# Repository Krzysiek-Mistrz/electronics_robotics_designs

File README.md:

# My Electronics Repository

Welcome to my electronics repository! This is the place where I store all my ppcbs, models and code for some of my projects1.

## Overview

This repository serves as a central hub for all the mechanical side of my robotic and automatic projects. It includes pcbs, models, and codes. Here, you will find a diverse collection of my works.

## Contents

The repository is organized by ECAD programs in which I have designed my PCBS and project type. In these folders you will find each project associated with this program. There's also models folder in which I have prepared all my models for my projects in CAD programs like SOLIDWORKS or INVENTOR.

- **Altium**
  - PCBs
- **Kicad**
  - PCBs
- **Models**
  - CAD models of robots
- **Codes**
  - Code for my projects

## Getting Started

To get started with any of the projects, follow these steps:

1. **Clone the repository**:
    ```bash
    git clone https://github.com/Krzysiek-Mistrz/<name_of_repo>.git
    ```

2. **Navigate to the project directory**:
    ```bash
    cd your-repo-name/project-directory
    ```

3. **Follow the specific project instructions**:
    Each project may have its own README file with detailed instructions on how to set up and run the code.

## Contributing

This repo is only showcase of my work, You don't have to contribute to it. If you have any suggestions on what should I improve please contact me via github :)

## Contact

If you have any questions or suggestions, feel free to reach out to me:
- GitHub: [Krzysiek-Mistrz](https://github.com/Krzysiek-Mistrz)

Thank you for visiting my repository! I hope you find the code here useful and informative.

## License

This repository is licensed under the GNU GPL V3. See the LICENSE file for more details.  

GNU GPL V3 @ Krzychu 2025

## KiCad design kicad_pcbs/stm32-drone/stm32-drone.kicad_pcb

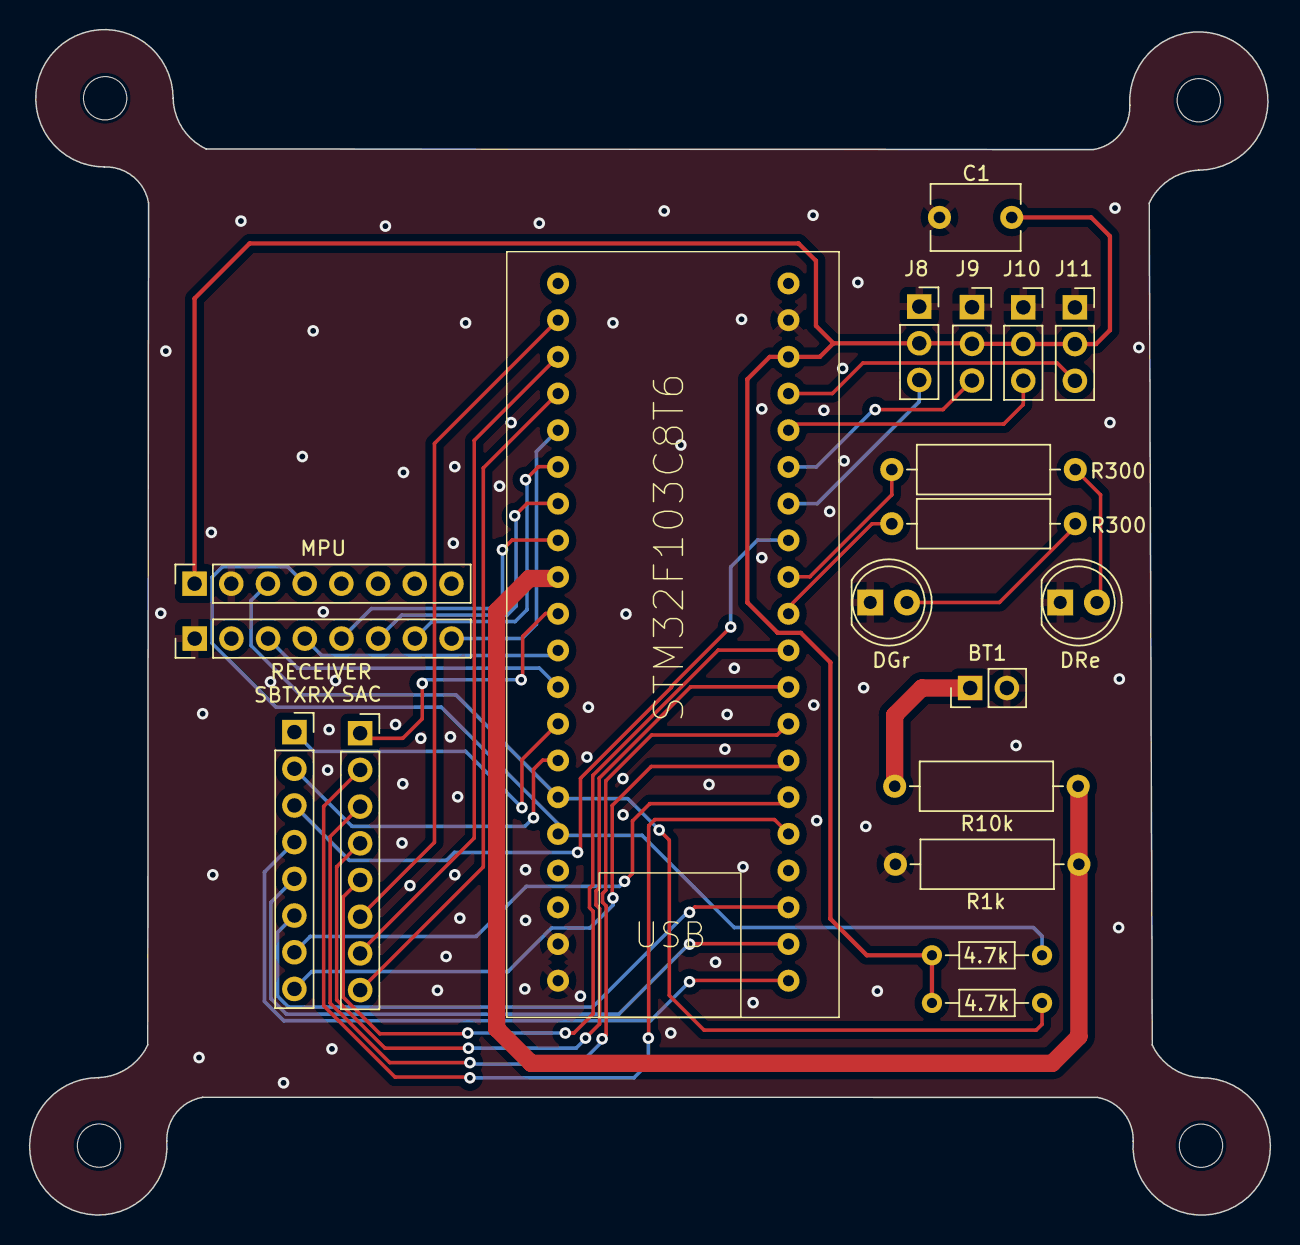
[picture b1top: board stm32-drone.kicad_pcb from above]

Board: 2 copper layers, 85.9 x 82.1 mm, 19 parts (0 on the bottom side), 36 nets.

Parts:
4.7k, 4.7k#2: 4.7k; R_Axial_DIN0204_L3.6mm_D1.6mm_P7.62mm_Horizontal
BT1: Battery; PinHeader_1x02_P2.54mm_Vertical
C1: C; C_Disc_D6.0mm_W4.4mm_P5.00mm
DGr: LED; LED_D5.0mm
DRe: LED; LED_D5.0mm
J6: RECEIVER; PinHeader_1x08_P2.54mm_Vertical
J8: ESC1 VGS; PinSocket_1x03_P2.54mm_Vertical
J9: ESC2 VGS; PinSocket_1x03_P2.54mm_Vertical
J10: ESC3 VGS; PinSocket_1x03_P2.54mm_Vertical
J11: ESC4 VGS; PinSocket_1x03_P2.54mm_Vertical
MPU: mpu6050 socket pins; PinSocket_1x08_P2.54mm_Vertical
R1k, R10k, R300, R300#2: R; R_Axial_DIN0309_L9.0mm_D3.2mm_P12.70mm_Horizontal
SAC: connector socket 1; PinSocket_1x08_P2.54mm_Vertical
SBTXRX: connector socket 2; PinSocket_1x08_P2.54mm_Vertical
U1: STM32F103C8Tx; stm32f103

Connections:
+5V: 4.7k.1, 4.7k#2.1, C1.1, J8.2, J9.2, J10.2, J11.2, MPU.1, U1.24 (VDD)
/BATT_ANALOG: R1k.2, R10k.1, U1.14 (PA4)
/C13: SAC.6, U1.2 (PC13)
/C14: SAC.7, U1.3 (PC14)
/C15: SAC.8, U1.4 (PC15)
/CH1: J6.8, U1.10 (PA0)
/CH2: J6.7, U1.11 (PA1)
/CH3: J6.6, U1.12 (PA2)
/CH4: J6.5, U1.13 (PA3)
/CH5: J6.4, U1.16 (PA6)
/CH6: J6.3, U1.17 (PA7)
/ESC1: J8.3, U1.42 (PB6)
/ESC2: J9.3, U1.43 (PB7)
/ESC3: J10.3, U1.45 (PB8)
/ESC4: J11.3, U1.46 (PB9)
/PA5: SAC.1, U1.15 (PA5)
/PA8: SAC.2, U1.29 (PA8)
/PA11: SAC.3, U1.32 (PA11)
/PA12: SAC.4, U1.33 (PA12)
/PA15: SAC.5, U1.38 (PA15)
/PB0: SBTXRX.1, U1.18 (PB0)
/PB1: SBTXRX.2, U1.19 (PB1)
/PB3: R300.1, U1.39 (PB3)
/PB4: R300#2.1, U1.40 (PB4)
/PB5: SBTXRX.3, U1.41 (PB5)
/PB12: SBTXRX.4, U1.25 (PB12)
/PB13: SBTXRX.5, U1.26 (PB13)
/PB14: SBTXRX.6, U1.27 (PB14)
/RX: SBTXRX.7, U1.30 (PA9)
/SCL: 4.7k.2, MPU.3, U1.21 (PB10)
/SDA: 4.7k#2.2, MPU.4, U1.22 (PB11)
/TX: SBTXRX.8, U1.31 (PA10)
GND: BT1.2 (-), C1.2, DGr.1 (K), DRe.1 (K), J6.1, J8.1, J9.1, J10.1, J11.1, MPU.2, R1k.1, U1.23 (VSS)
unnamed: DGr.2 (A), R300.2
unnamed: DRe.2 (A), R300#2.2
VCC: BT1.1 (+), R10k.2

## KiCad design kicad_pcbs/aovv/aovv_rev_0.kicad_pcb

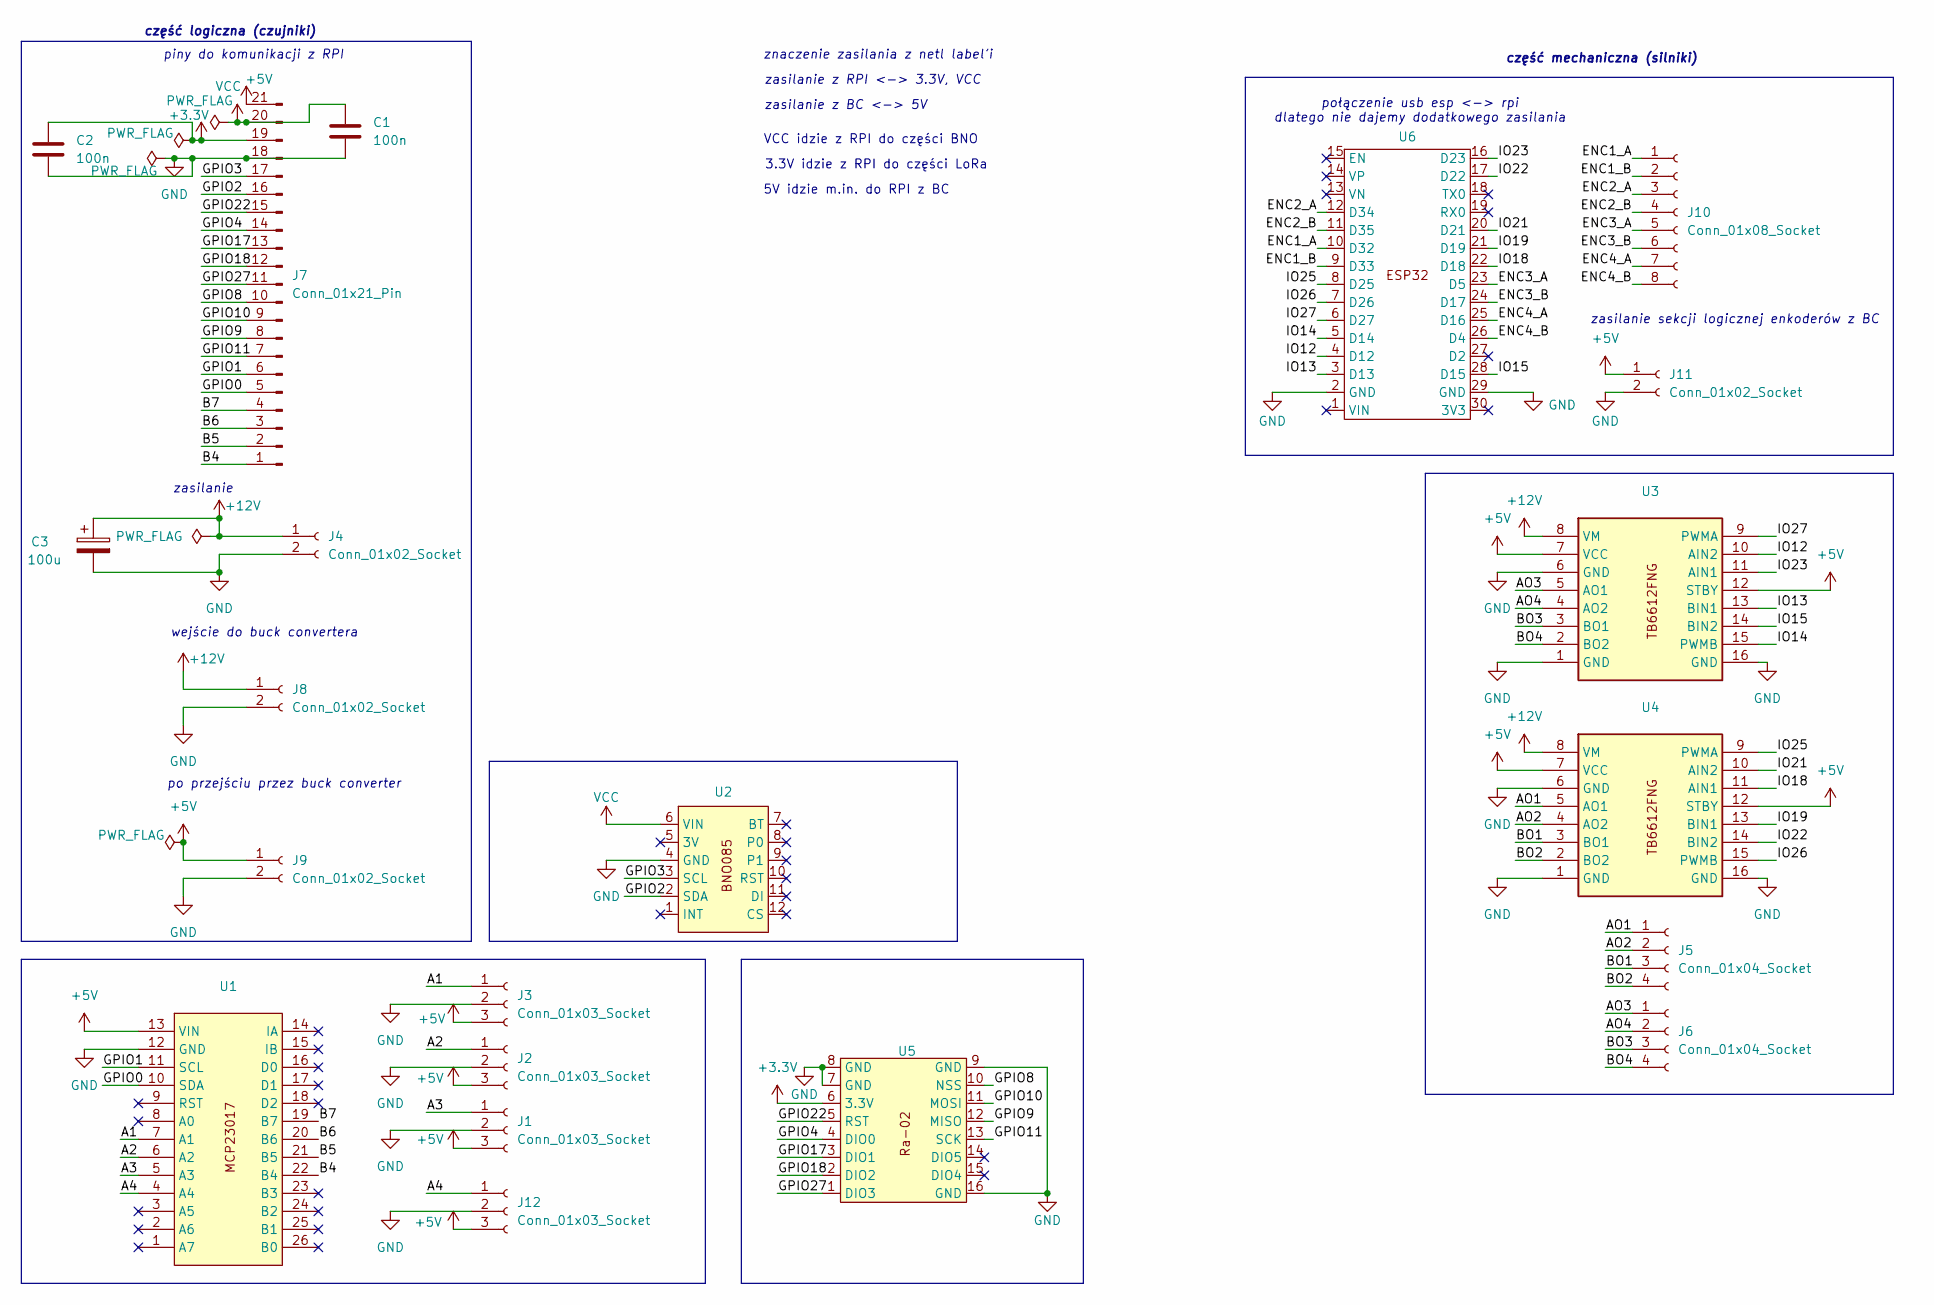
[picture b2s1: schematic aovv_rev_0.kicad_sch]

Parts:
C1, C2: 100n; C_Disc_D11.0mm_W5.0mm_P5.00mm
C3: 100u; CP_Radial_D8.0mm_P2.50mm
J1, J2, J3, J12: Conn_01x03_Socket; PinSocket_1x03_P2.54mm_Vertical
J4, J8, J9, J11: Conn_01x02_Socket; PinSocket_1x02_P2.54mm_Vertical
J5, J6: Conn_01x04_Socket; PinSocket_1x04_P2.54mm_Vertical
J7: Conn_01x21_Pin; PinHeader_1x21_P2.54mm_Vertical
J10: Conn_01x08_Socket; PinSocket_1x08_P2.54mm_Vertical
U1: MCP23017_THT
U2: BNO085_THT
U3, U4: TB6612FNG_THT
U5: Ra-02_THT
U6: ESP32_THT

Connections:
+3.3V: C2.2, J7.19, U5.6 (3.3V)
+5V: J1.3, J2.3, J3.3, J7.21, J9.1, J11.1, J12.3, U1.13 (VIN), U3.7 (VCC), U3.12 (STBY), U4.7 (VCC), U4.12 (STBY)
+12V: C3.1, J4.1, J8.1, U3.8 (VM), U4.8 (VM)
/A1: J3.1, U1.7 (A1)
/A2: J2.1, U1.6 (A2)
/A3: J1.1, U1.5 (A3)
/A4: J12.1, U1.4 (A4)
/AO1: J5.1, U4.5 (AO1)
/AO2: J5.2, U4.4 (AO2)
/AO3: J6.1, U3.5 (AO1)
/AO4: J6.2, U3.4 (AO2)
/B4: J7.1, U1.22 (B4)
/B5: J7.2, U1.21 (B5)
/B6: J7.3, U1.20 (B6)
/B7: J7.4, U1.19 (B7)
/BO1: J5.3, U4.3 (BO1)
/BO2: J5.4, U4.2 (BO2)
/BO3: J6.3, U3.3 (BO1)
/BO4: J6.4, U3.2 (BO2)
/ENC1_A: J10.1, U6.10 (D32)
/ENC1_B: J10.2, U6.9 (D33)
/ENC2_A: J10.3, U6.12 (D34)
/ENC2_B: J10.4, U6.11 (D35)
/ENC3_A: J10.5, U6.23 (D5)
/ENC3_B: J10.6, U6.24 (D17)
/ENC4_A: J10.7, U6.25 (D16)
/ENC4_B: J10.8, U6.26 (D4)
/GPIO0: J7.5, U1.10 (SDA)
/GPIO1: J7.6, U1.11 (SCL)
/GPIO2: J7.16, U2.2 (SDA)
/GPIO3: J7.17, U2.3 (SCL)
/GPIO4: J7.14, U5.4 (DIO0)
/GPIO8: J7.10, U5.10 (NSS)
/GPIO9: J7.8, U5.12 (MISO)
/GPIO10: J7.9, U5.11 (MOSI)
/GPIO11: J7.7, U5.13 (SCK)
/GPIO17: J7.13, U5.3 (DIO1)
/GPIO18: J7.12, U5.2 (DIO2)
/GPIO22: J7.15, U5.5 (RST)
/GPIO27: J7.11, U5.1 (DIO3)
/IO12: U3.10 (AIN2), U6.4 (D12)
/IO13: U3.13 (BIN1), U6.3 (D13)
/IO14: U3.15 (PWMB), U6.5 (D14)
/IO15: U3.14 (BIN2), U6.28 (D15)
/IO18: U4.11 (AIN1), U6.22 (D18)
/IO19: U4.13 (BIN1), U6.21 (D19)
/IO21: U4.10 (AIN2), U6.20 (D21)
/IO22: U4.14 (BIN2), U6.17 (D22)
/IO23: U3.11 (AIN1), U6.16 (D23)
/IO25: U4.9 (PWMA), U6.8 (D25)
/IO26: U4.15 (PWMB), U6.7 (D26)
/IO27: U3.9 (PWMA), U6.6 (D27)
GND: C1.2, C2.1, C3.2, J1.2, J2.2, J3.2, J4.2, J7.18, J8.2, J9.2, J11.2, J12.2, U1.12 (GND), U2.4 (GND), U3.1 (GND), U3.6 (GND), U3.16 (GND), U4.1 (GND), U4.6 (GND), U4.16 (GND), U5.7 (GND), U5.8 (GND), U5.9 (GND), U5.16 (GND), U6.2 (GND), U6.29 (GND)
VCC: C1.1, J7.20, U2.6 (VIN)

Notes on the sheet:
zasilanie z RPI <-> 3.3V, VCC
3.3V idzie z RPI do części LoRa
połączenie usb esp <-> rpi dlatego nie dajemy dodatkowego zasilania
zasilanie z BC <-> 5V
część logiczna (czujniki)
wejście do buck convertera
piny do komunikacji z RPI
VCC idzie z RPI do części BNO
zasilanie sekcji logicznej enkoderów z BC
znaczenie zasilania z netl label'i
część mechaniczna (silniki)
zasilanie
5V idzie m.in. do RPI z BC
po przejściu przez buck converter

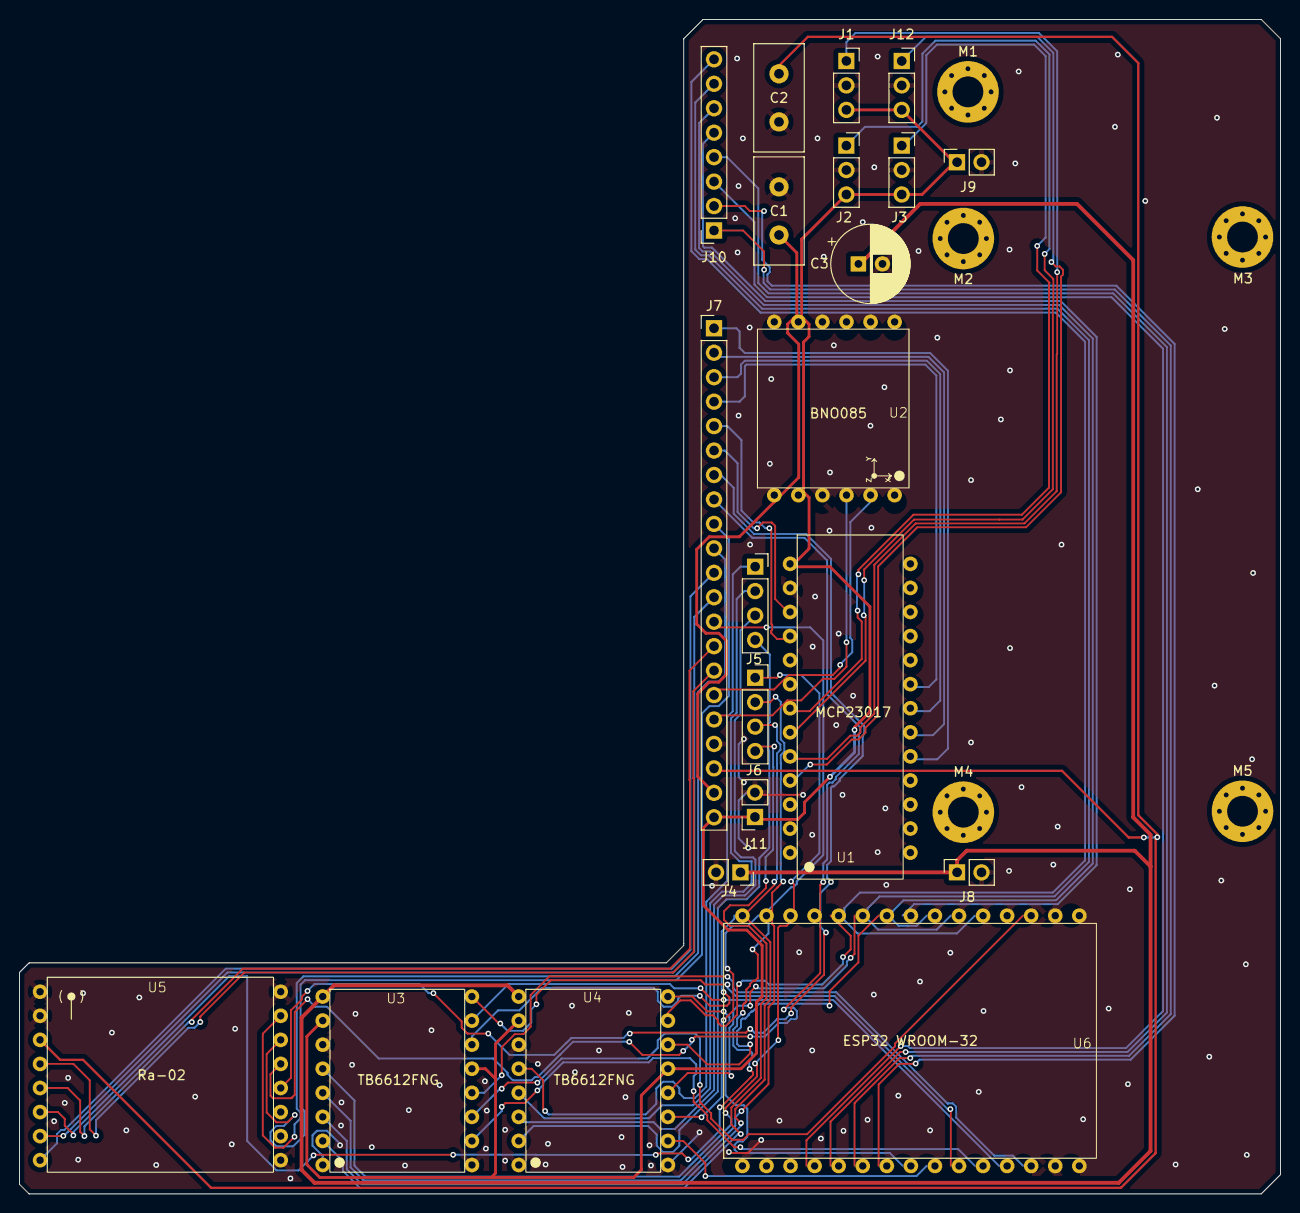
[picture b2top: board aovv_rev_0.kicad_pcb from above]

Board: 2 copper layers, 131.0 x 122.0 mm, 26 parts (0 on the bottom side), 54 nets.

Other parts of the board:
M1, M2, M3, M4, M5: MountingHole_3.2mm_M3_Pad_Via

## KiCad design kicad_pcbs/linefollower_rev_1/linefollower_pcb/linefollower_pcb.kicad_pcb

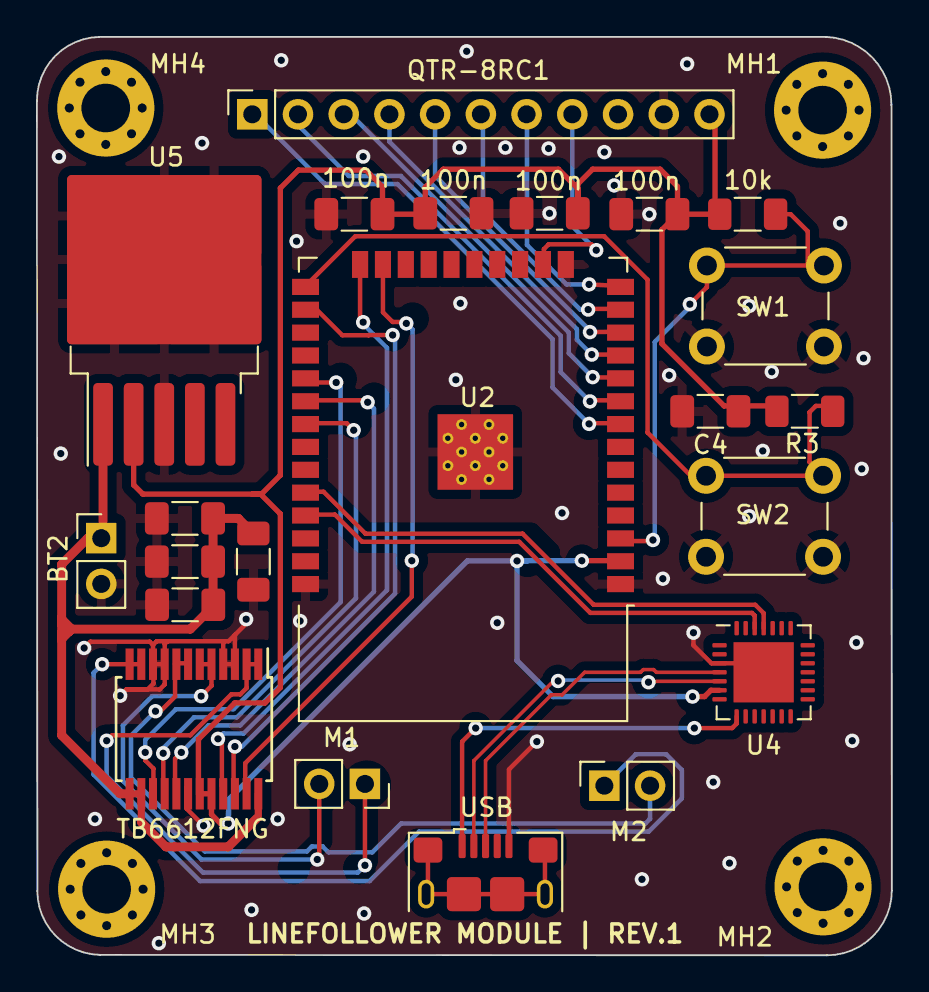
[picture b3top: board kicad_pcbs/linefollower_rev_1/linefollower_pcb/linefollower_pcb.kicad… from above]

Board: 2 copper layers, 47.5 x 51.0 mm, 26 parts (0 on the bottom side), 28 nets.

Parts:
10k: 10k; R_1206_3216Metric_Pad1.30x1.75mm_HandSolder
100n: C_Unpolarized; C_1206_3216Metric_Pad1.33x1.80mm_HandSolder
100n#2, 100n#3: C; C_1206_3216Metric_Pad1.33x1.80mm_HandSolder
100u1, 200u1: C_Polarized; C_1206_3216Metric_Pad1.33x1.80mm_HandSolder
BT2: Battery; PinHeader_1x02_P2.54mm_Vertical
C1, C5: 100n; C_1206_3216Metric_Pad1.33x1.80mm_HandSolder
C2, C4: 10u; C_1206_3216Metric_Pad1.33x1.80mm_HandSolder
M1, M2: Conn_01x02_Socket; PinSocket_1x02_P2.54mm_Vertical
MH1, MH2, MH3, MH4: MountingHole_2.7mm_Pad_Via
QTR-8RC1: Conn_01x11_Socket; PinSocket_1x11_P2.54mm_Vertical
R3: 10k; R_1206_3216Metric_Pad1.30x1.75mm_HandSolder
SW1, SW2: SW_Push; SW_PUSH_6mm
U1: TB6612FNG; SSOP-24_5.3x8.2mm_P0.65mm
U2: ESP32-WROOM-32
U4: CP2102N-Axx-xQFN28; QFN-28-1EP_5x5mm_P0.5mm_EP3.35x3.35mm
U5: LM2596S-3.3; TO-263-5_TabPin3
USB: USB_B_Micro; USB_Micro-B_Amphenol_10118193-0001LF_Horizontal

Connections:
/A1: M1.1, U1.1 (AO1), U1.2 (AO1)
/A2: M1.2, U1.5 (AO2), U1.6 (AO2)
/B1: M2.1, U1.11 (BO1), U1.12 (BO1)
/B2: M2.2, U1.7 (BO2), U1.8 (BO2)
/BOOT: R3.1, SW2.1, U2.25 (IO0)
/D2: U1.21 (AIN1), U2.24 (IO2)
/D4: U1.22 (AIN2), U2.26 (IO4)
/D5: U1.15 (PWMB), U2.29 (IO5)
/D12: QTR-8RC1.7, U2.14 (IO12)
/D13: QTR-8RC1.8, U2.16 (IO13)
/D14: QTR-8RC1.6, U2.13 (IO14)
/D15: U1.23 (PWMA), U2.23 (IO15)
/D18: U1.17 (BIN1), U2.30 (IO18)
/D19: U1.16 (BIN2), U2.31 (IO19)
/D25: QTR-8RC1.3, U2.10 (IO25)
/D26: QTR-8RC1.4, U2.11 (IO26)
/D27: QTR-8RC1.5, U2.12 (IO27)
/D32: QTR-8RC1.1, U2.8 (IO32)
/D33: QTR-8RC1.2, U2.9 (IO33)
/D+: U4.4 (D+), USB.3 (D+)
/D-: U4.5 (D-), USB.2 (D-)
/EN: 10k.1, SW1.1, U2.3 (EN)
/RX: U2.34 (RXD0/IO3), U4.25 (RXD)
/TX: U2.35 (TXD0/IO1), U4.26 (TXD)
/VBUS: U4.8 (VBUS), USB.1 (VBUS)
GND: 100n.2, 100n#2.2, 100n#3.2, 100u1.2, 200u1.2, BT2.2 (-), C1.2, C2.2, C4.2, C5.1, QTR-8RC1.10, SW1.2, SW2.2, U1.3 (PGND1), U1.4 (PGND1), U1.9 (PGND2), U1.10 (PGND2), U1.18 (GND), U2.1 (GND), U2.15 (GND), U2.38 (GND), U2.39 (GND), U4.3 (GND), U4.29 (GND), U5.3 (GND), USB.5 (GND)
VCC: 10k.2, 100n.1, 100n#2.1, 100n#3.1, C4.1, C5.2, QTR-8RC1.11, R3.2, U1.19 (STBY), U1.20 (VCC), U2.2 (VDD), U4.6 (VDD), U5.2 (OUT)
VDD: 100u1.1, 200u1.1, BT2.1 (+), C1.1, C2.1, U1.13 (VM2), U1.14 (VM3), U1.24 (VM1), U5.1 (VIN)

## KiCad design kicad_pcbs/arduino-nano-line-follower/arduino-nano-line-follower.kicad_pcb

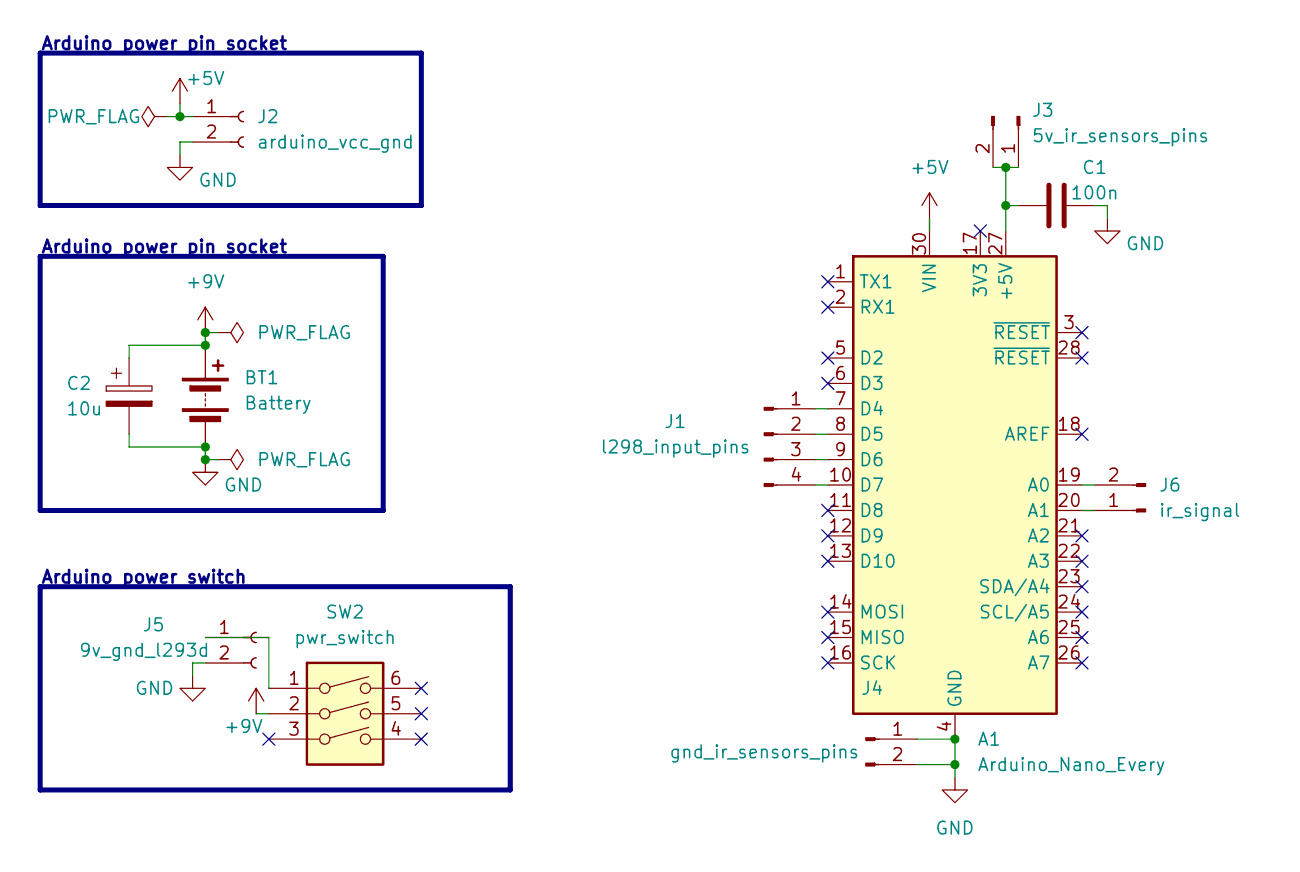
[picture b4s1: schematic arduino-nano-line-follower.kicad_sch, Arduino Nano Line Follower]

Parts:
A1: Arduino_Nano_Every; Arduino_Nano
BT1: Battery; PinSocket_1x02_P2.54mm_Vertical
C1: 100n; C_Disc_D3.0mm_W1.6mm_P2.50mm
C2: 10u; C_Radial_D4.0mm_H5.0mm_P1.50mm
J1: l298_input_pins; PinHeader_1x04_P2.54mm_Vertical
J2: arduino_vcc_gnd; PinSocket_1x02_P2.54mm_Vertical
J3: 5v_ir_sensors_pins; PinHeader_1x02_P2.54mm_Vertical
J4: gnd_ir_sensors_pins; PinHeader_1x02_P2.54mm_Vertical
J5: 9v_gnd_l293d; PinSocket_1x02_P2.54mm_Vertical
J6: ir_signal; PinHeader_1x02_P2.54mm_Vertical
SW2: pwr_switch; SW_NKK_G1xJP

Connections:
+5V: A1.30 (VIN), J2.1
+9V: BT1.1 (+), C2.1, SW2.2
GND: A1.4 (GND), A1.29 (GND), BT1.2 (-), C1.2, C2.2, J2.2, J4.1, J4.2, J5.2; also elsewhere on the board
unnamed: A1.27 (+5V), C1.1, J3.1, J3.2
unnamed: A1.19 (A0), J6.2
unnamed: A1.20 (A1), J6.1
unnamed: A1.7 (D4), J1.1
unnamed: A1.8 (D5), J1.2
unnamed: A1.9 (D6), J1.3
unnamed: A1.10 (D7), J1.4
unnamed 10: J5.1, SW2.1; also elsewhere on the board

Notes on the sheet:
Arduino power pin socket
Arduino power switch

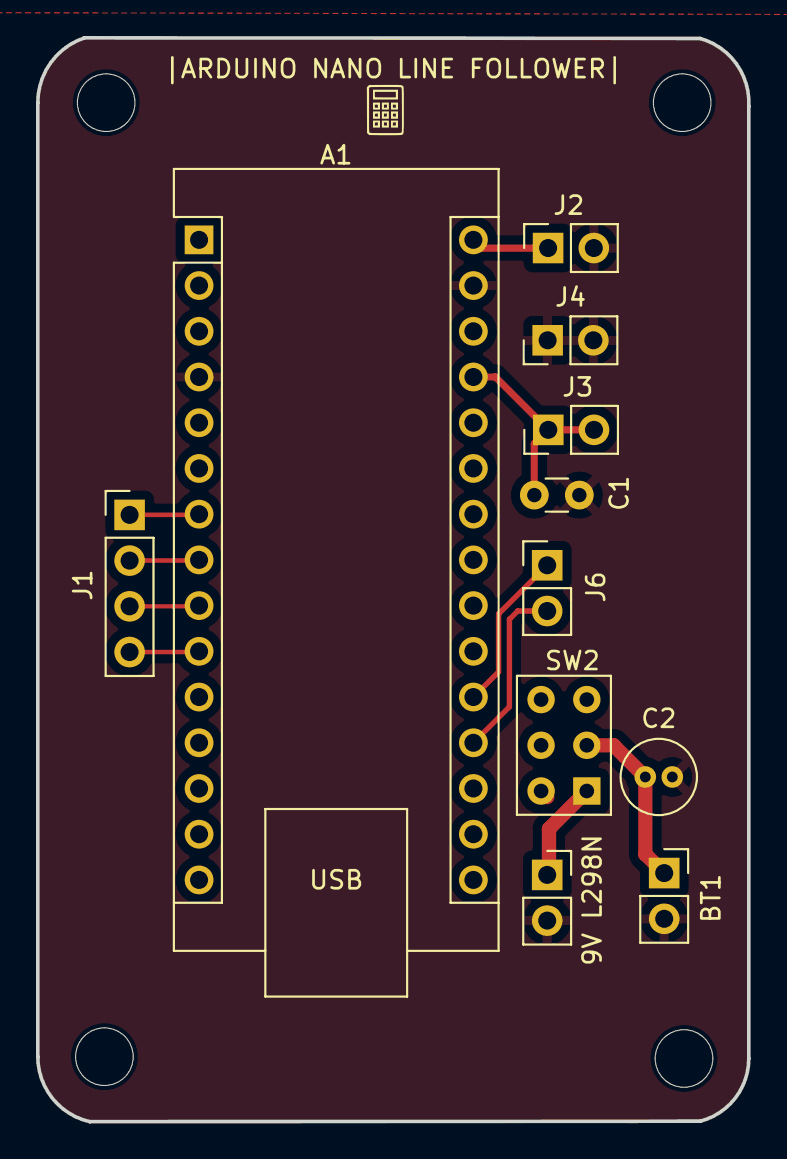
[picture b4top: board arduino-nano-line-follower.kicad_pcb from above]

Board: 2 copper layers, 39.5 x 60.2 mm, 11 parts (0 on the bottom side), 11 nets.

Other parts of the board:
9V L298N: 9v_gnd_l293d; PinSocket_1x02_P2.54mm_Vertical

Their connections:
GND: 9V L298N.2; also elsewhere on the board
unnamed 10: 9V L298N.1; also elsewhere on the board

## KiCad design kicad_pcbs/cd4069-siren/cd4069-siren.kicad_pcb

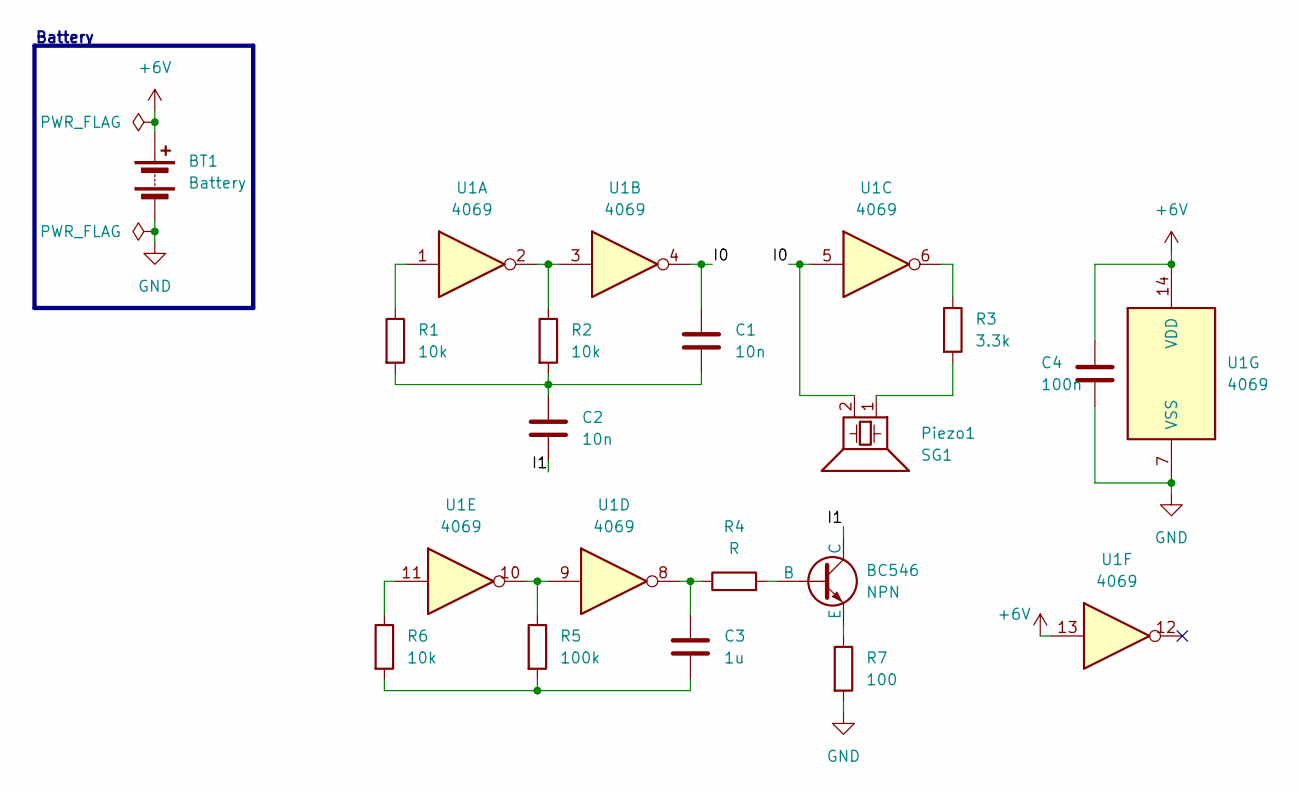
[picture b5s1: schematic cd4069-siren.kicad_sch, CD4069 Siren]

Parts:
BC546: NPN; TO-92
BT1: Battery; PinHeader_1x02_P2.54mm_Vertical
C1, C2: 10n; C_Disc_D3.0mm_W1.6mm_P2.50mm
C3: 1u; C_Disc_D3.0mm_W1.6mm_P2.50mm
C4: 100n; C_Disc_D3.0mm_W1.6mm_P2.50mm
Piezo1: SG1; Buzzer_12x9.5RM7.6
R1, R2, R6: 10k; R_Axial_DIN0204_L3.6mm_D1.6mm_P7.62mm_Horizontal
R3: 3.3k; R_Axial_DIN0204_L3.6mm_D1.6mm_P7.62mm_Horizontal
R4: R; R_Axial_DIN0204_L3.6mm_D1.6mm_P7.62mm_Horizontal
R5: 100k; R_Axial_DIN0204_L3.6mm_D1.6mm_P7.62mm_Horizontal
R7: 100; R_Axial_DIN0204_L3.6mm_D1.6mm_P7.62mm_Horizontal
U1: 4069; DIP-14_W7.62mm

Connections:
+6V: BT1.1 (+), C4.1, U1.13, U1.14 (VDD); also elsewhere on the board
/I0: C1.1, Piezo1.2, U1.4, U1.5; also elsewhere on the board
/I1: BC546.1 (C), C2.2
GND: BT1.2 (-), C4.2, R7.2, U1.7 (VSS); also elsewhere on the board
unnamed: BC546.2 (B), R4.2
unnamed: BC546.3 (E), R7.1
unnamed: C1.2, C2.1, R1.2, R2.2
unnamed 7: C3.1, R4.1, U1.8; also elsewhere on the board
unnamed: C3.2, R5.2, R6.2
unnamed: Piezo1.1, R3.2
unnamed 10: R1.1, U1.1; also elsewhere on the board
unnamed 11: R2.1, U1.2, U1.3; also elsewhere on the board
unnamed 12: R3.1, U1.6; also elsewhere on the board
unnamed 13: R5.1, U1.9, U1.10; also elsewhere on the board
unnamed 14: R6.1, U1.11; also elsewhere on the board

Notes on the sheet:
Battery

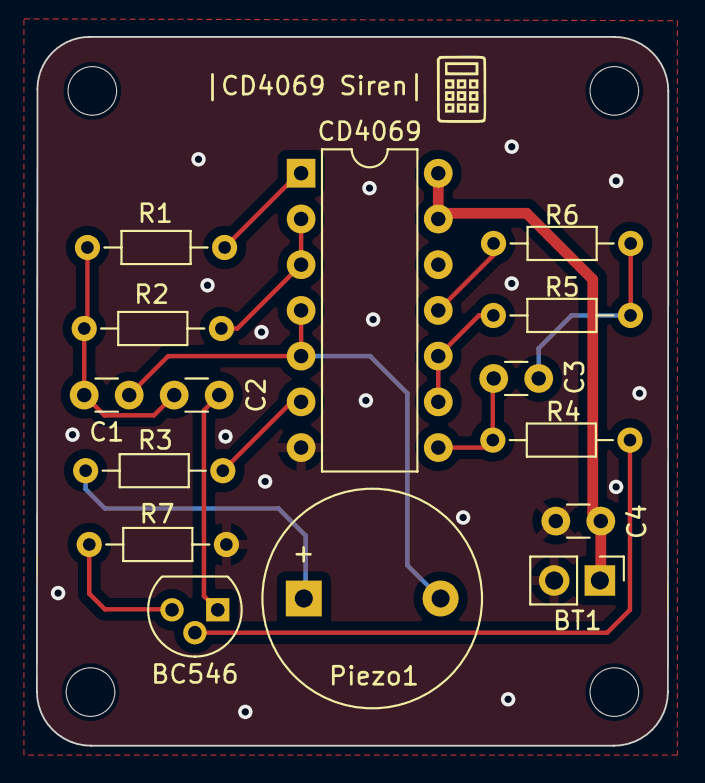
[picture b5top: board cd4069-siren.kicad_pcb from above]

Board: 2 copper layers, 35.1 x 39.4 mm, 15 parts (0 on the bottom side), 15 nets.

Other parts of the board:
CD4069: 4069; DIP-14_W7.62mm

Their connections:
+6V: CD4069.13, CD4069.14 (VDD); also elsewhere on the board
/I0: CD4069.4, CD4069.5; also elsewhere on the board
GND: CD4069.7 (VSS); also elsewhere on the board
unnamed 7: CD4069.8; also elsewhere on the board
unnamed 10: CD4069.1; also elsewhere on the board
unnamed 11: CD4069.2, CD4069.3; also elsewhere on the board
unnamed 12: CD4069.6; also elsewhere on the board
unnamed 13: CD4069.9, CD4069.10; also elsewhere on the board
unnamed 14: CD4069.11; also elsewhere on the board

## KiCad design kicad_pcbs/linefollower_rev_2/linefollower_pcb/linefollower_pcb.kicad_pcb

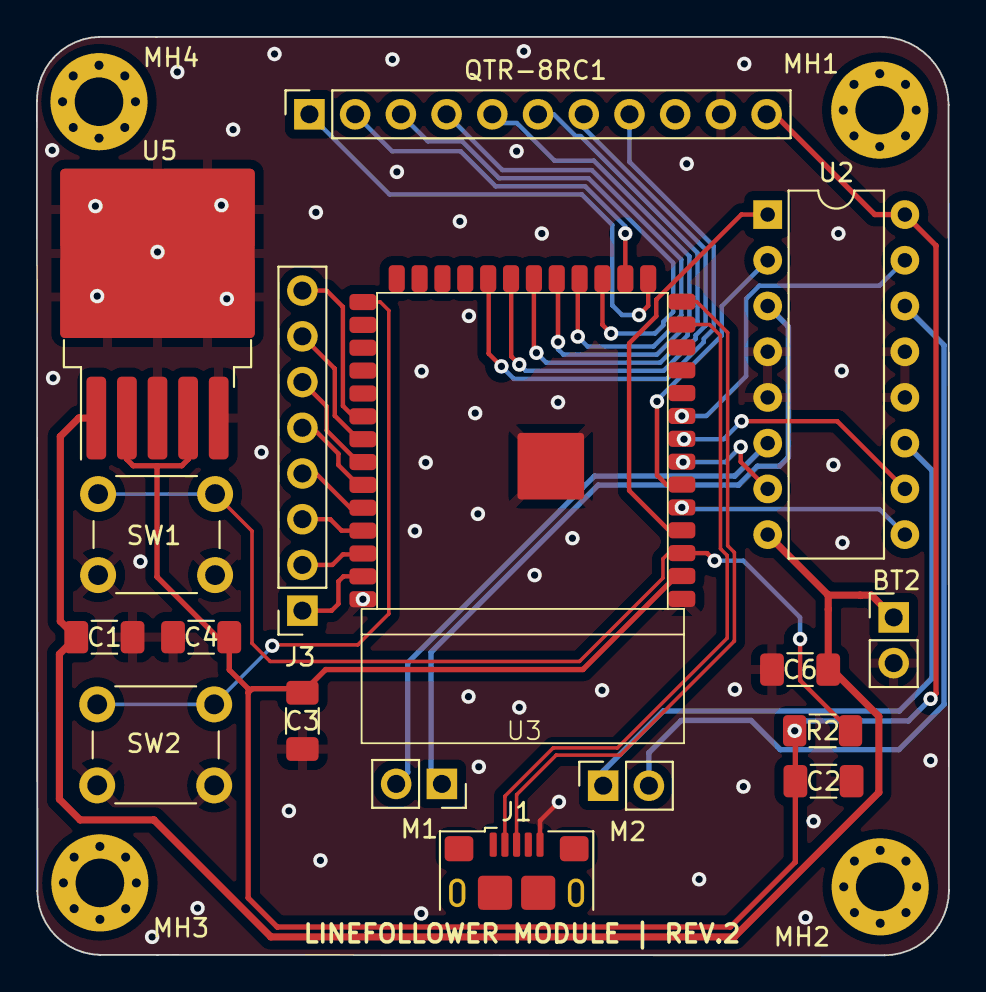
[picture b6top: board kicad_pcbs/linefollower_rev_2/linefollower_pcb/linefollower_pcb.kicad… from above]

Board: 2 copper layers, 50.7 x 51.0 mm, 21 parts (0 on the bottom side), 33 nets.

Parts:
BT2: Battery; PinHeader_1x02_P2.54mm_Vertical
C1, C4: 100n; C_1206_3216Metric_Pad1.33x1.80mm_HandSolder
C2, C6: 10u; C_1206_3216Metric_Pad1.33x1.80mm_HandSolder
C3: C_Unpolarized; C_1206_3216Metric_Pad1.33x1.80mm_HandSolder
J1: USB_B_Micro; USB_Micro-B_Amphenol_10118193-0001LF_Horizontal
J3: Conn_01x08_Socket; PinSocket_1x08_P2.54mm_Vertical
M1, M2: Conn_01x02_Socket; PinSocket_1x02_P2.54mm_Vertical
MH1, MH2, MH3, MH4: MountingHole_2.7mm_Pad_Via
QTR-8RC1: Conn_01x11_Socket; PinSocket_1x11_P2.54mm_Vertical
R2: 10k; R_1206_3216Metric_Pad1.30x1.75mm_HandSolder
SW1, SW2: SW_Push; SW_PUSH_6mm
U2: L293D; DIP-16_W7.62mm
U3: esp3_s3_wroom_1
U5: LM2596S-3.3; TO-263-5_TabPin3

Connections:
/A1: M1.1, U2.3 (1Y)
/A2: M1.2, U2.6 (2Y)
/B1: M2.1, U2.11 (3Y)
/B2: M2.2, U2.14 (4Y)
/BOOT: SW2.1, U3.27 (IO0)
/D+: J1.3 (D+), U3.14 (IO20)
/D-: J1.2 (D-), U3.13 (IO19)
/EN: R2.2, SW1.1, U3.3 (EN)
/IO1: J3.1, U3.39 (IO1)
/IO2: J3.2, U3.38 (IO2)
/IO3: QTR-8RC1.1, U3.15 (IO3)
/IO4: U2.1 (EN1,2), U3.4 (IO4)
/IO5: U2.9 (EN3,4), U3.5 (IO5)
/IO6: U2.2 (1A), U3.6 (IO6)
/IO7: U2.7 (2A), U3.7 (IO7)
/IO9: QTR-8RC1.3, U3.17 (IO9)
/IO10: QTR-8RC1.4, U3.18 (IO10)
/IO11: QTR-8RC1.5, U3.19 (IO11)
/IO12: QTR-8RC1.6, U3.20 (IO12)
/IO13: QTR-8RC1.7, U3.21 (IO13)
/IO14: QTR-8RC1.8, U3.22 (IO14)
/IO15: U2.10 (3A), U3.8 (IO15)
/IO16: U2.15 (4A), U3.9 (IO16)
/IO39: J3.8, U3.32 (IO39)
/IO40: J3.7, U3.33 (IO40)
/IO41: J3.6, U3.34 (IO41)
/IO42: J3.5, U3.35 (IO42)
/IO46: QTR-8RC1.2, U3.16 (IO46)
/RXD0: J3.4, U3.36 (RXD0)
/TXD0: J3.3, U3.37 (TXD0)
GND: BT2.2 (-), C1.2, C2.2, C3.2, C4.2, C6.2, J1.5 (GND), QTR-8RC1.10, SW1.2, SW2.2, U2.4 (GND), U2.5 (GND), U2.12 (GND), U2.13 (GND), U3.1 (GND), U3.40 (GND), U3.41 (GND), U5.3 (GND), U5.5 (~ON/OFF)
VCC: C2.1, C3.1, C4.1, QTR-8RC1.11, R2.1, U2.16 (VCC1), U3.2 (3V3), U5.2 (OUT), U5.4 (FB)
VDD: BT2.1 (+), C1.1, C6.1, U2.8 (VCC2), U5.1 (VIN)

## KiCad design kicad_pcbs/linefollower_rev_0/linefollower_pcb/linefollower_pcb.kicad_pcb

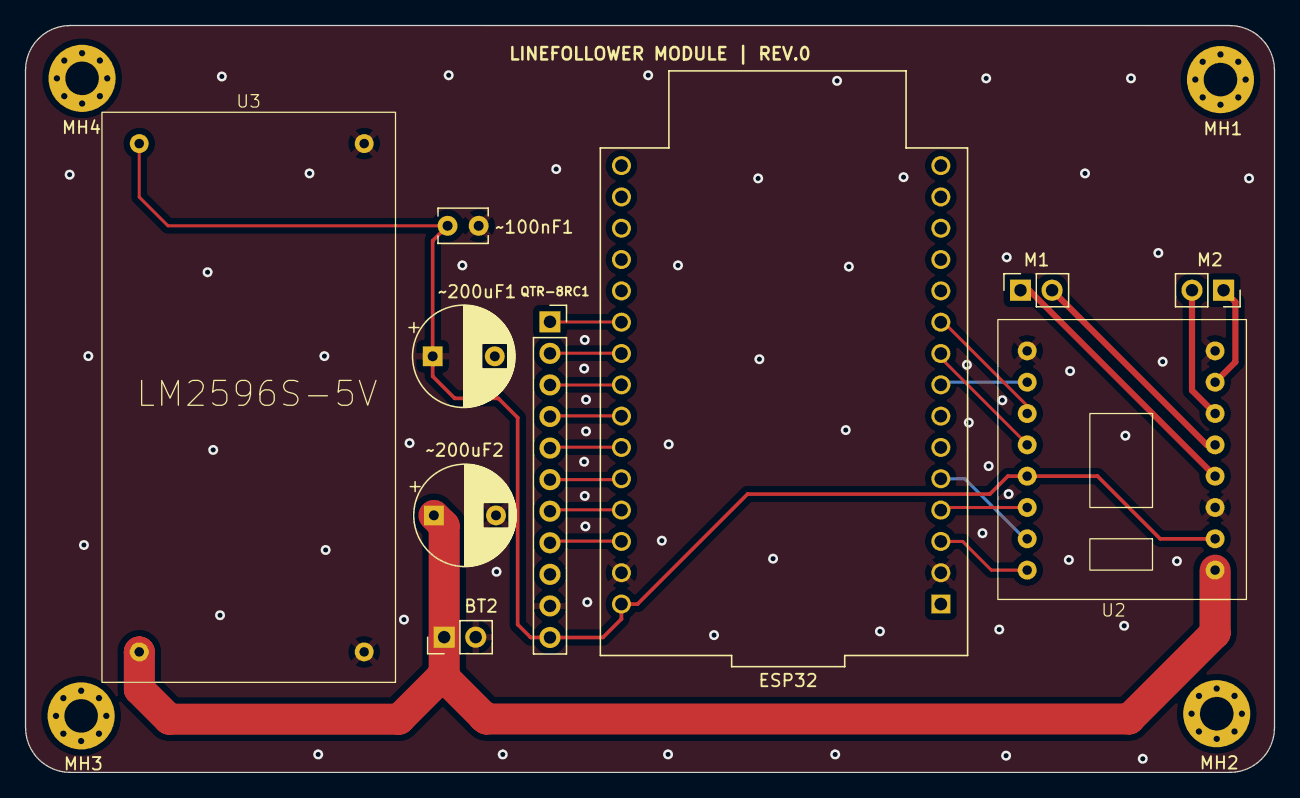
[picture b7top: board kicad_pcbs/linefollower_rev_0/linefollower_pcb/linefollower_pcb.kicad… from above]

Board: 2 copper layers, 100.5 x 60.1 mm, 11 parts (0 on the bottom side), 21 nets.

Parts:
BT2: Battery; PinHeader_1x02_P2.54mm_Vertical
ESP32: ESP32-DEVKITC; MODULE_ESP32-DEVKITC
M1, M2: Conn_01x02_Socket; PinSocket_1x02_P2.54mm_Vertical
MH1, MH2, MH3, MH4: MountingHole_2.7mm_Pad_Via
QTR-8RC1: Conn_01x11_Socket; PinSocket_1x11_P2.54mm_Vertical
U2: TB6612FNG; TB6612FNG_DEV_KIT
U3: LM2596S_DEV_KIT

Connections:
/A1: M1.1, U2.1 (AO1)
/A2: M1.2, U2.5 (AO2)
/B1: M2.1, U2.11 (BO1)
/B2: M2.2, U2.7 (BO2)
/D2: ESP32.24 (IO2), U2.21 (AIN1)
/D4: ESP32.26 (IO4), U2.22 (AIN2)
/D5: ESP32.29 (IO5), U2.15 (PWMB)
/D12: ESP32.13 (IO12), QTR-8RC1.7
/D13: ESP32.15 (IO13), QTR-8RC1.8
/D14: ESP32.12 (IO14), QTR-8RC1.6
/D15: ESP32.23 (IO15), U2.23 (PWMA)
/D18: ESP32.30 (IO18), U2.17 (BIN1)
/D19: ESP32.31 (IO19), U2.16 (BIN2)
/D25: ESP32.9 (IO25), QTR-8RC1.3
/D26: ESP32.10 (IO26), QTR-8RC1.4
/D27: ESP32.11 (IO27), QTR-8RC1.5
/D32: ESP32.7 (IO32), QTR-8RC1.1
/D33: ESP32.8 (IO33), QTR-8RC1.2
GND: BT2.2 (-), ESP32.14 (GND1), ESP32.32 (GND2), QTR-8RC1.10, U2.3 (PGND1), U2.9 (PGND2), U2.18 (GND), U3.1 (IN-), U3.3 (OUT-)
VCC: ESP32.19 (EXT_5V), QTR-8RC1.11, U2.19 (STBY), U2.20 (VCC), U3.4 (OUT+)
VDD: BT2.1 (+), U2.24 (VM1), U3.2 (IN+)
